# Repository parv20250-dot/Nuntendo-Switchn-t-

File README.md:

# Nuntendo-Switchn-t-
Hello hello hello person who has stumbled onto my GitHub repository, I'm so glad that you're here, before I go into my project some background on the name because I find it funny - I was initially thinking of designing a gaming console that runs existing games (like a switch)when I realised that that's too complex for me as of now ,so we improvise adapt overcome around here presentingggg the <ins>Nuntendo Switchn't <ins>,it is a gaming console containing games coded by yours truly, meee. The name itself is a pun and an abbreviation for nun (nothing)like a Nintendo, not a switch. Throughout this repository you will see my attempt at running a console that runs basic games such as pong,tetris,snake and maybe(if time permits and my coding abilities prevail) a subway surfer inspired endless runner.

Watch as I try to build a functional handheld gaming console on a budget and hopefully end up with something that doesn't spontaneously disappoint me or go kaboom.

This is what the 3d case looks like obvioo I'll add a display but thats for later.

It also uses a pcb, a VERY VERY VERY messy one but still

##Firmare
I coded the games myself in Arduino C++

This was created as a hack club project for halflife

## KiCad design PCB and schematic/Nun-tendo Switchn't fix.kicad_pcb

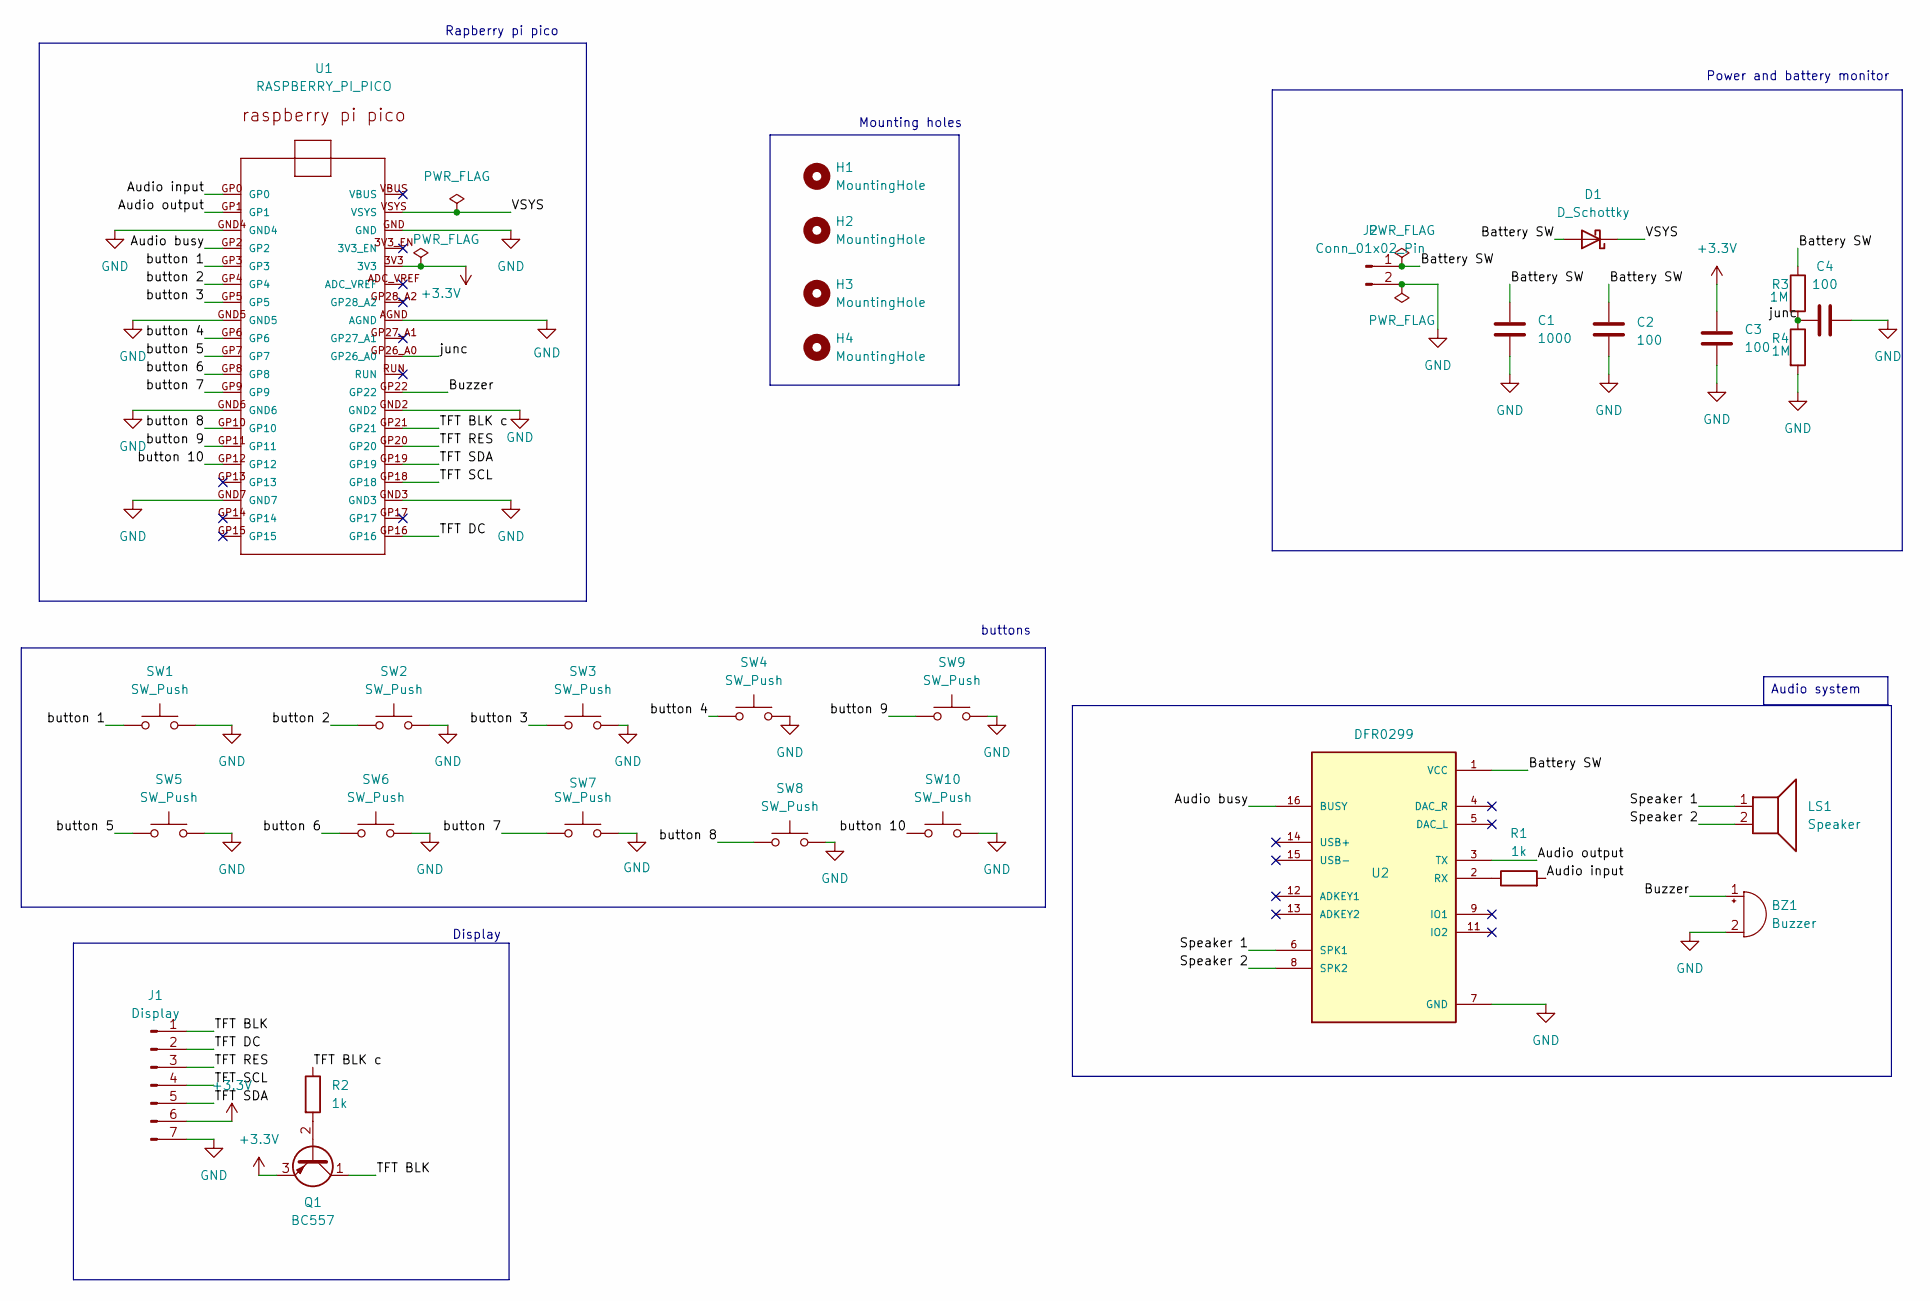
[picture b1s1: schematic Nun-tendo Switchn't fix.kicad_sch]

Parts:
BZ1: Buzzer; Buzzer_TDK_PS1240P02BT_D12.2mm_H6.5mm
C1: 1000; CP_Radial_D10.0mm_P5.00mm
C2, C4: 100; C_Disc_D5.0mm_W2.5mm_P2.50mm
C3: 100; C_Disc_D4.7mm_W2.5mm_P5.00mm
D1: D_Schottky; D_DO-34_SOD68_P7.62mm_Horizontal
H1, H2, H3, H4: MountingHole; MountingHole_2.7mm_M2.5
J1: Display; PinHeader_1x07_P2.54mm_Vertical
J2: Conn_01x02_Pin; PinHeader_1x02_P2.54mm_Vertical
LS1: Speaker; PinHeader_1x02_P2.54mm_Vertical
Q1: BC557; TO-92_Inline
R1, R2: 1k; R_Axial_DIN0207_L6.3mm_D2.5mm_P7.62mm_Horizontal
R3, R4: 1M; R_Axial_DIN0207_L6.3mm_D2.5mm_P7.62mm_Horizontal
SW1, SW2, SW3, SW4, SW5, SW6, SW7, SW8, SW9, SW10: SW_Push; SW_PUSH_6mm_H4.3mm
U1: RASPBERRY_PI_PICO
U2: DFR0299; MODULE_DFR0299

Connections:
+3.3V: C3.1, J1.6, Q1.3 (E), U1.3V3
/Audio busy: U1.GP2, U2.16 (BUSY)
/Audio input: R1.2, U1.GP0
/Audio output: U1.GP1, U2.3 (TX)
/Battery SW: C1.1, C2.1, D1.2 (A), J2.1, R3.1, U2.1 (VCC)
/Buzzer: BZ1.1 (+), U1.GP22
/Speaker 1: LS1.1, U2.6 (SPK1)
/Speaker 2: LS1.2, U2.8 (SPK2)
/TFT BLK: J1.1, Q1.1 (C)
/TFT BLK c: R2.1, U1.GP21
/TFT DC: J1.2, U1.GP16
/TFT RES: J1.3, U1.GP20
/TFT SCL: J1.4, U1.GP18
/TFT SDA: J1.5, U1.GP19
/VSYS: D1.1 (K), U1.VSYS
/button 1: SW1.1, U1.GP3
/button 2: SW2.1, U1.GP4
/button 3: SW3.1, U1.GP5
/button 4: SW4.1, U1.GP6
/button 5: SW5.1, U1.GP7
/button 6: SW6.1, U1.GP8
/button 7: SW7.1, U1.GP9
/button 8: SW8.1, U1.GP10
/button 9: SW9.1, U1.GP11
/button 10: SW10.1, U1.GP12
GND: BZ1.2 (-), C1.2, C2.2, C3.2, C4.2, J1.7, J2.2, R4.2, SW1.2, SW2.2, SW3.2, SW4.2, SW5.2, SW6.2, SW7.2, SW8.2, SW9.2, SW10.2, U1.AGND, U1.GND, U1.GND2, U1.GND3, U1.GND4, U1.GND5, U1.GND6, U1.GND7, U2.7 (GND), U2.10 (GND)
unnamed: C4.1, R3.2, R4.1, U1.GP26_A0
unnamed: Q1.2 (B), R2.2
unnamed: R1.1, U2.2 (RX)

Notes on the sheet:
Display
Power and battery monitor
Mounting holes
Rapberry pi pico
buttons
Audio system

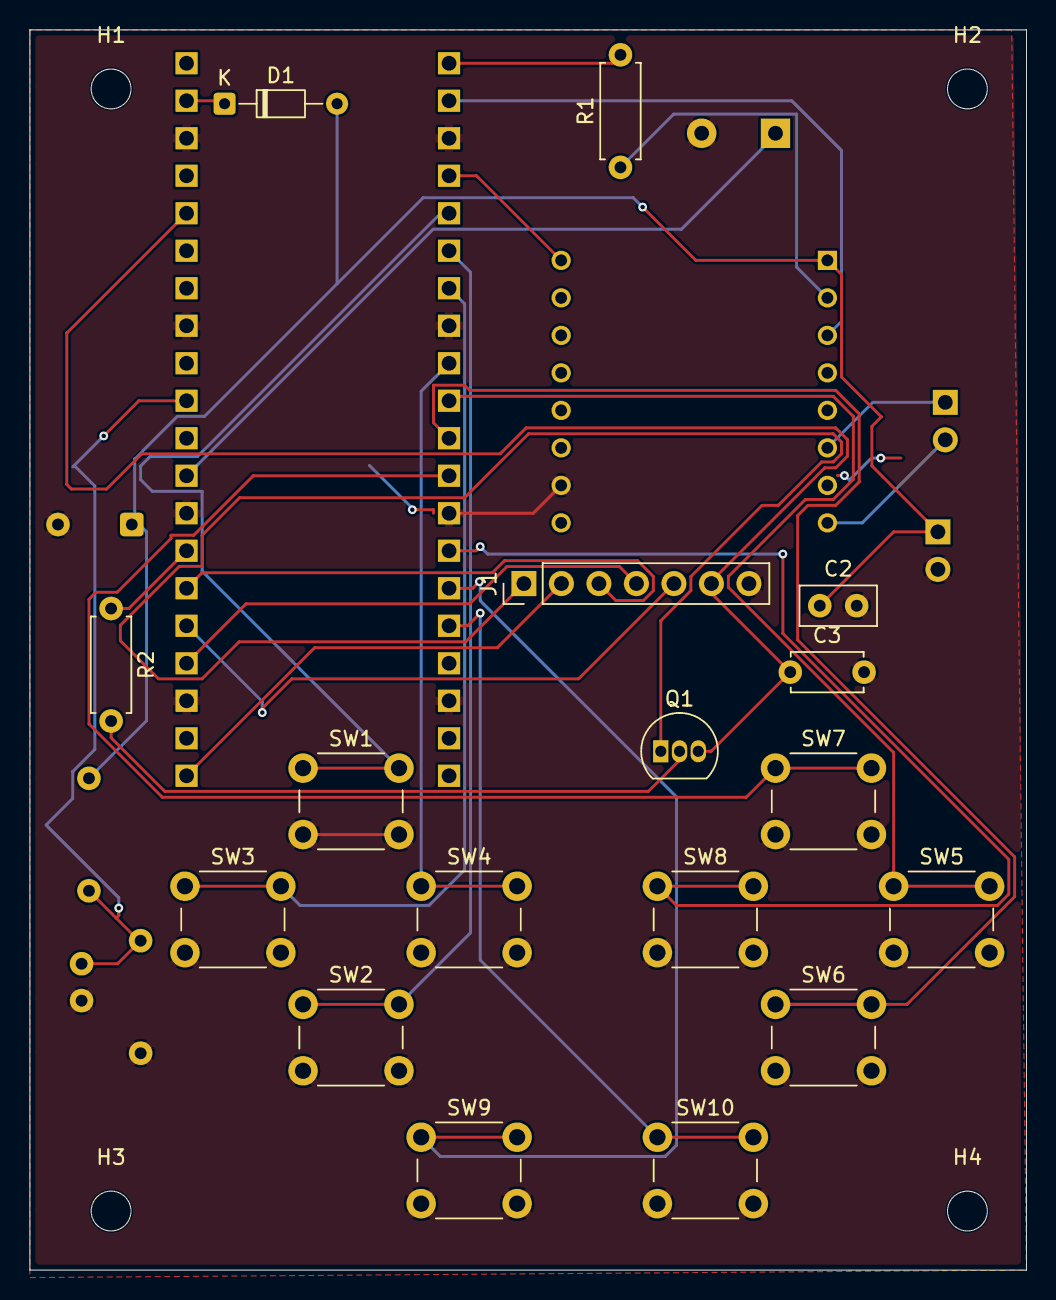
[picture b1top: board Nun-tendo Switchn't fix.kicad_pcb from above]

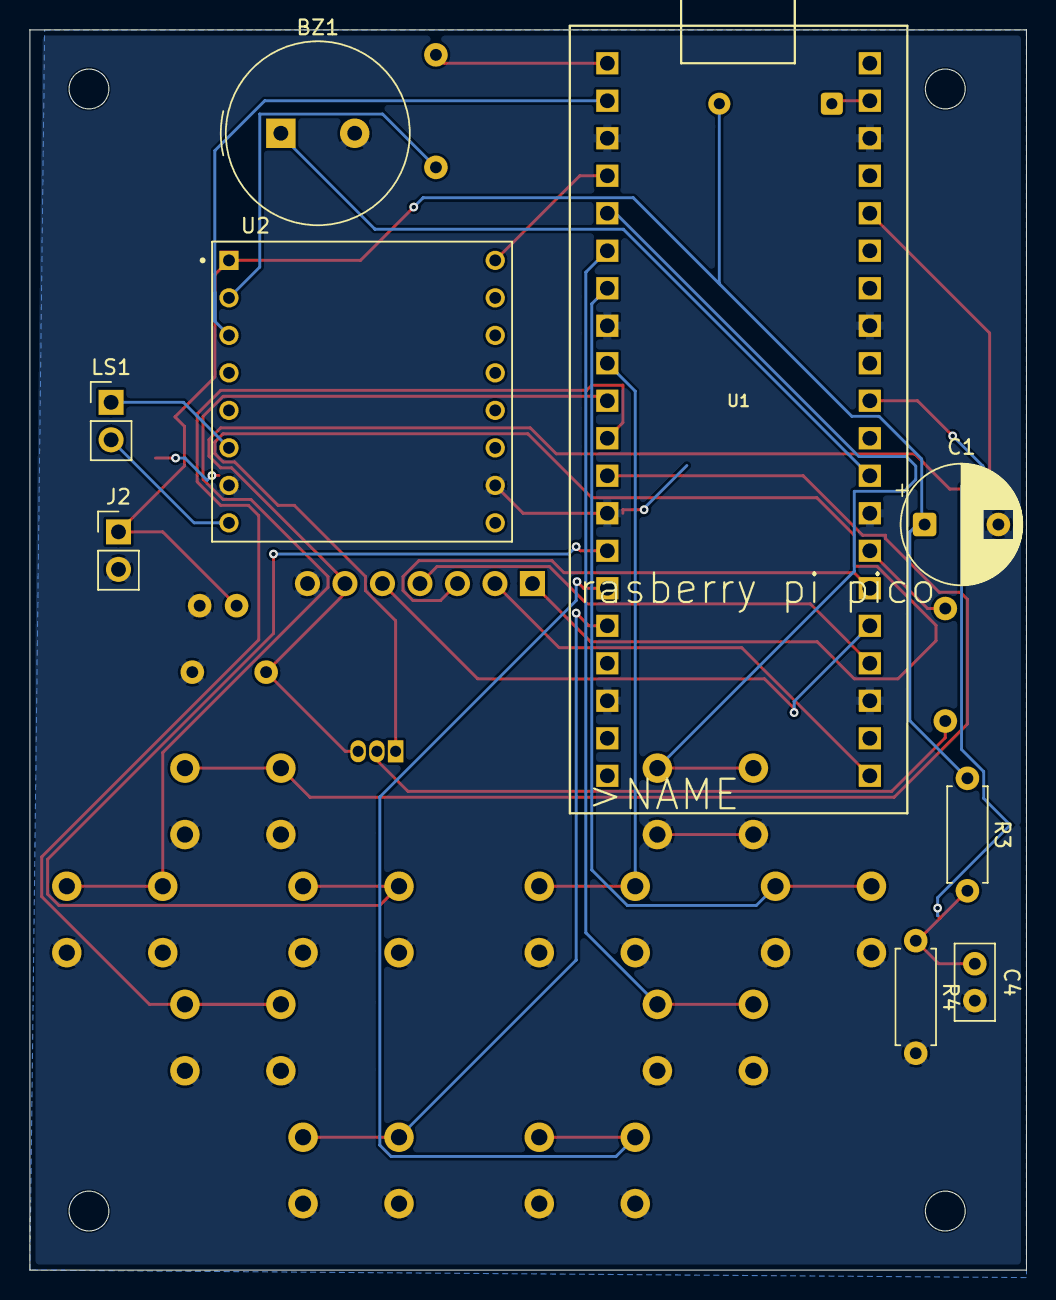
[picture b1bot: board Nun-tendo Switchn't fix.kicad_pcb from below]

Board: 2 copper layers, 67.5 x 84.0 mm, 30 parts (9 on the bottom side), 29 nets.
